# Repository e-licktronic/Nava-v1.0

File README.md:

# Nava-v1.0-code
An attempt to fix some of the remaining NAVA Firmware bugs and add some features I wanted for own use.

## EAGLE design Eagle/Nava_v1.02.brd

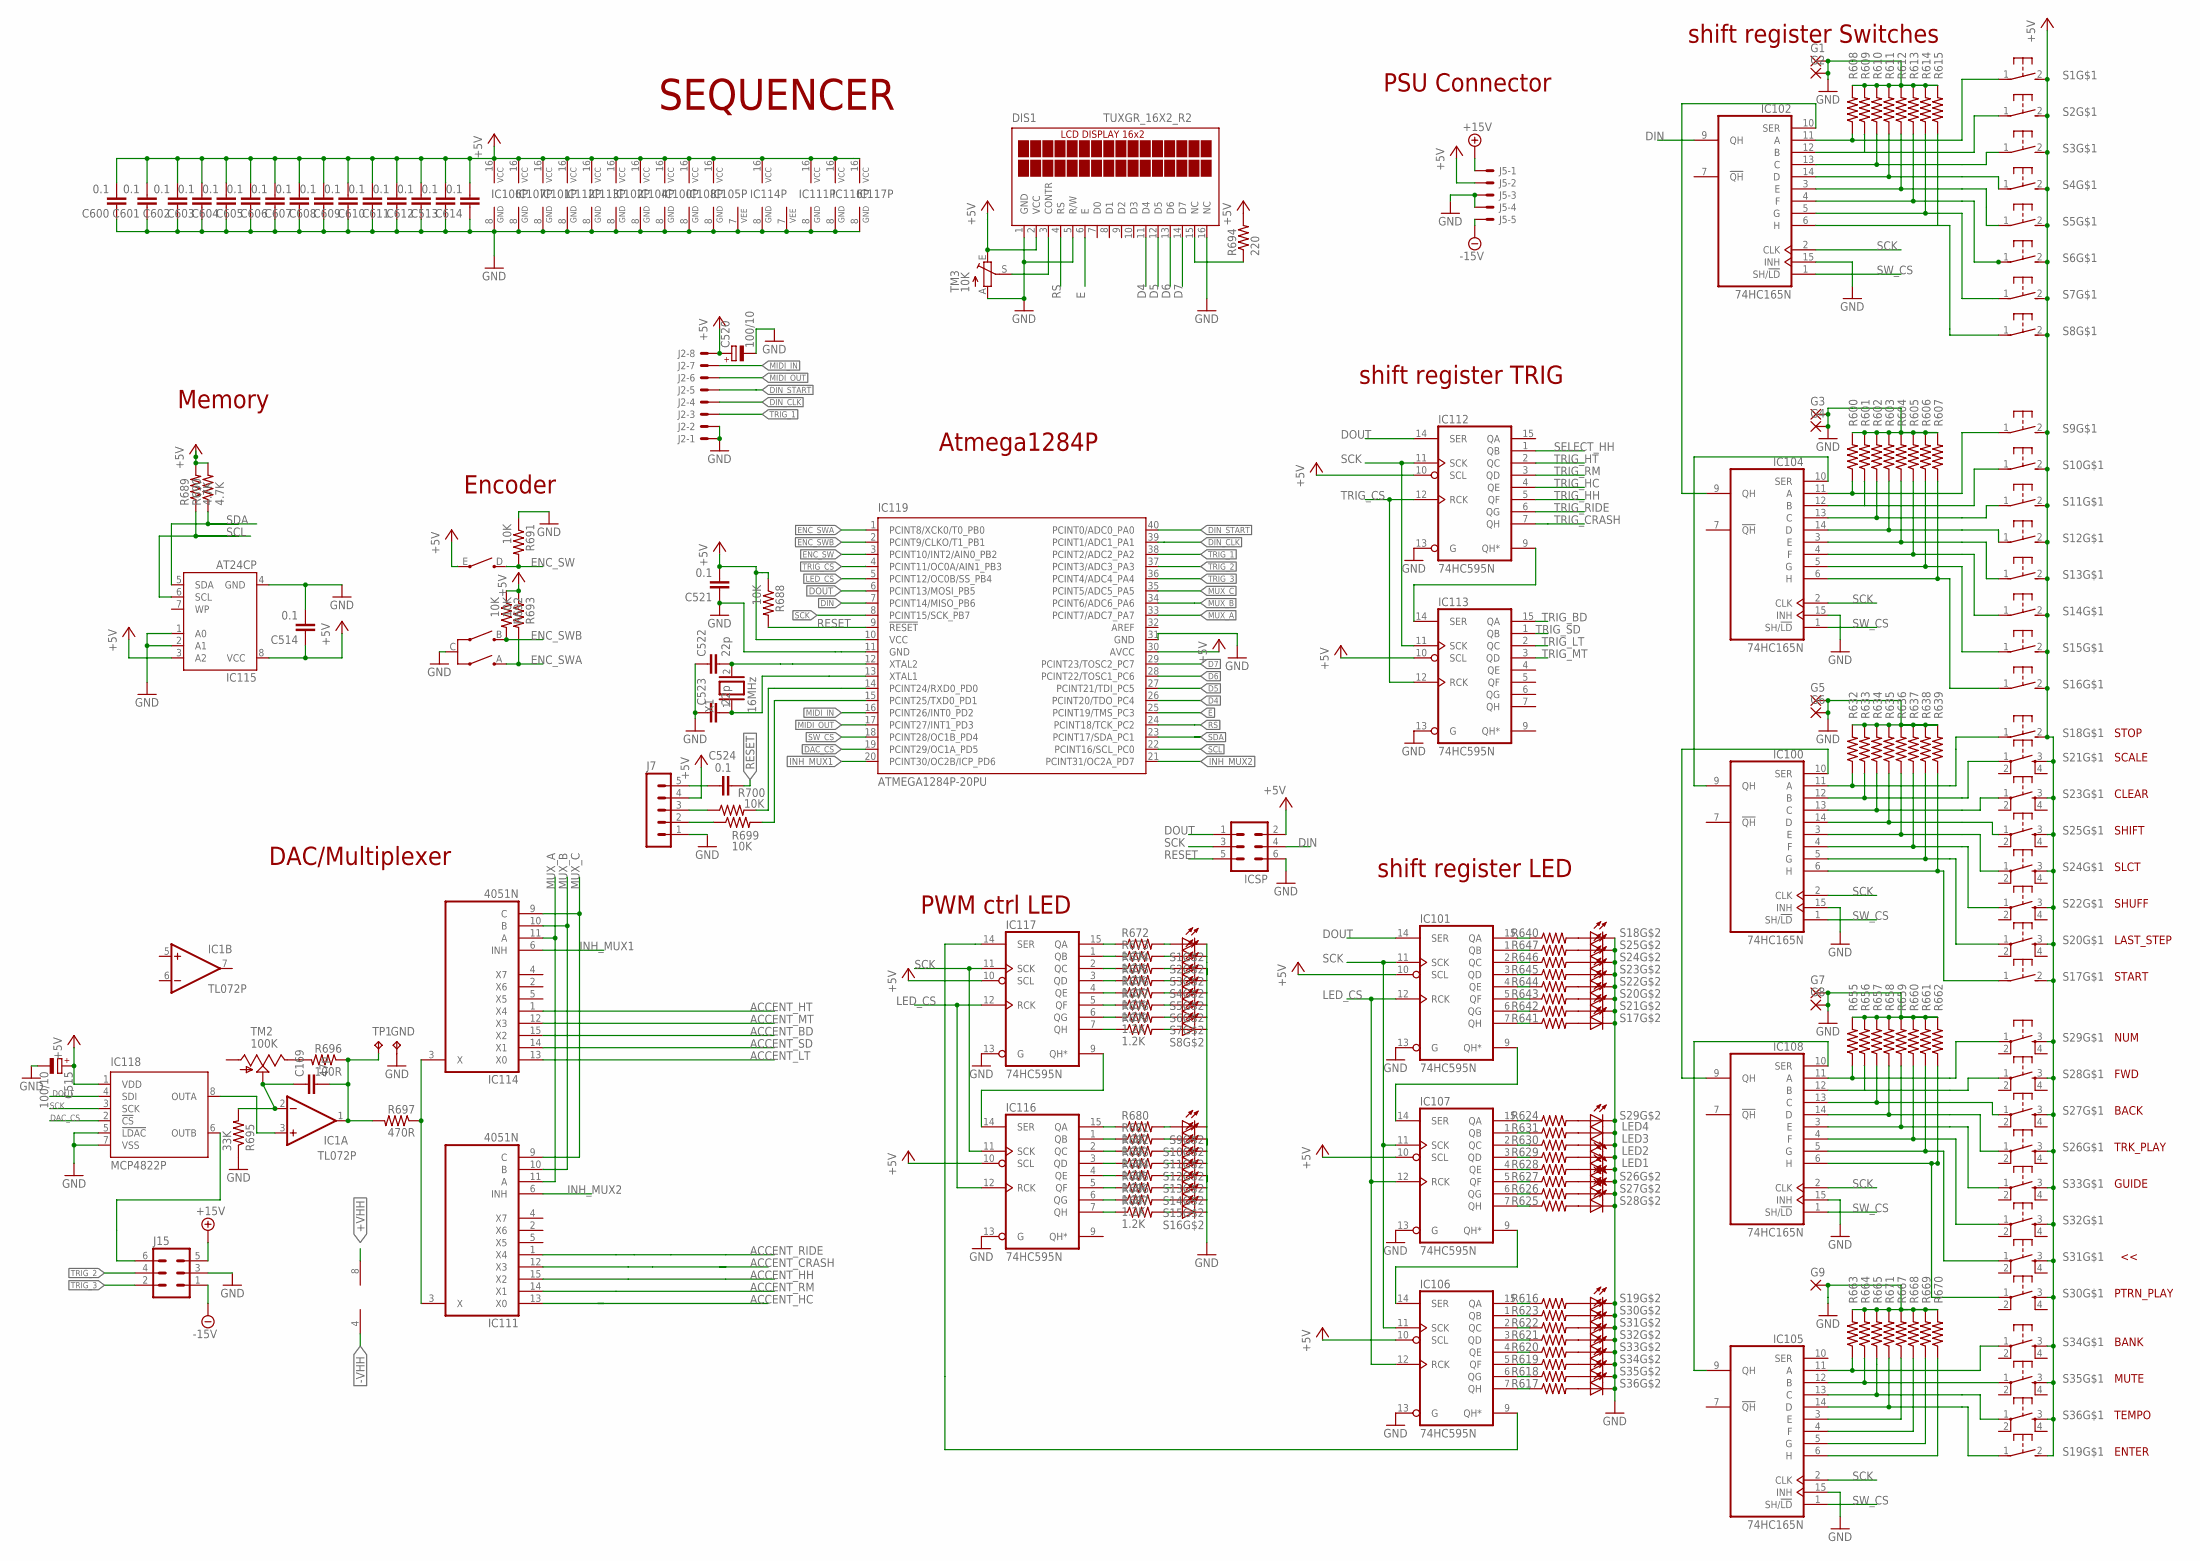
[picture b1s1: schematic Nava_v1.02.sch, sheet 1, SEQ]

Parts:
C169: 47p; C025-025X050
C513, C514, C521, C524, C600, C601, C602, C603, C604, C605, C606, C607, C608, C609, C610, C611, C612, C614: 0.1; C050-024X044
C515, C520: 100/10; E2-5
C522, C523: 22p; C025-025X050
DIS1: TUXGR_16X2_R2
G1, G2, G3, G4, G5, G6, G7, G8, G9: WIREPAD1,6/0,8; 1,6/0,8
GND: TPPAD1-13; P1-13
IC1: TL072P; DIL08
IC100, IC102, IC104, IC105, IC108: 74HC165N; DIL16
IC101, IC106, IC107, IC112, IC113, IC116, IC117: 74HC595N; DIL16
IC111, IC114: 4051N; DIL16
IC115: AT24CP; DIL08
IC118: MCP4822P; DIL8
IC119: ATMEGA1284P-20PU; DIL40
ICSP: MA03-2
J2: 22-27-2081-08; 6410-08
J5: KK-156-5
J7: MA05-1; MA05-1A
J15: MA03-2
LED1, LED2, LED3, LED4: LED3MM
R600, R601, R602, R603, R604, R605, R606, R607, R608, R609, R610, R611, R612, R613, R614, R615, R632, R633, R634, R635, R636, R637, R638, R639, R655, R656, R657, R658, R659, R660, R661, R662, R663, R664, R665, R667, R668, R669, R670, R671, R688, R691, R692, R693, R699, R700: 10K; 0207/7
R616, R617, R618, R619, R620, R621, R622, R623, R624, R625, R626, R627, R628, R629, R630, R631, R640, R641, R642, R643, R644, R645, R646, R647, R672, R673, R674, R675, R676, R677, R678, R679, R680, R681, R682, R683, R684, R685, R686, R687: 1.2K; 0207/7
R689, R690: 4.7K; 0207/7
R694: 220; 0207/7
R695: 33K; 0207/7
R696: 100R; 0207/7
R697: 470R; 0207/7
S1, S2, S3, S4, S5, S6, S7, S8, S9, S10, S11, S12, S13, S14, S15, S16, S17, S18, S19: MX1A_CHERRY_SW_LED"; MX1A-SW
S20, S21, S22, S23, S24, S25, S26, S27, S28, S29, S30, S31, S32, S33, S34, S35, S36: ZTSN_SW_LED"; SPH_SW
TM2: 100K; S64W
TM3: 10K; B25P
TP1: TPPAD1-13; P1-13
VR29: PEC16_ENCODER
X1: 16MHz; QS

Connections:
+5V: C513.2, C514.1, C515.+, C520.+, C521.2, C600.2, C601.2, C602.2, C603.2, C604.2, C605.2, C606.2, C607.2, C608.2, C609.2, C610.2, C611.2, C612.2, C614.2, DIS1.2 (VCC), IC100.16 (VCC), IC101.10 (SCL), IC101.16 (VCC), IC102.16 (VCC), IC104.16 (VCC), IC105.16 (VCC), IC106.10 (SCL), IC106.16 (VCC), IC107.10 (SCL), IC107.16 (VCC), IC108.16 (VCC), IC111.16 (VCC), IC112.10 (SCL), IC112.16 (VCC), IC113.10 (SCL), IC113.16 (VCC), IC114.16 (VCC), IC115.3 (A2), IC115.8 (VCC), IC116.10 (SCL), IC116.16 (VCC), IC117.10 (SCL), IC117.16 (VCC), IC118.1 (VDD), IC119.10 (VCC), IC119.30 (AVCC), ICSP.2, J2.8, J5.2, J7.4, R688.1, R689.2, R690.2, R692.1, R693.1, R694.2, S1.2 (S), S2.2 (S), S3.2 (S), S4.2 (S), S5.2 (S), S6.2 (S), S7.2 (S), S8.2 (S), S9.2 (S), S10.2 (S), S11.2 (S), S12.2 (S), S13.2 (S), S14.2 (S), S15.2 (S), S16.2 (S), S17.2 (S), S18.2 (S), S19.2 (S), S20.3 (S), S22.3 (S), S23.3 (S), S24.3 (S), S25.3 (S), S26.3 (S), S27.3 (S), S28.3 (S), S29.3 (S), S30.3 (S), S31.3 (S), S32.3 (S), S33.3 (S), S34.3 (S), S35.3 (S), S36.3 (S), TM3.E, VR29.E; also elsewhere on the board
+15V: J5.1, J15.5; also elsewhere on the board
+VHH: IC1.8 (V+); also elsewhere on the board
-15V: J5.5, J15.1; also elsewhere on the board
-VHH: IC1.4 (V-); also elsewhere on the board
ACCENT_BD: IC114.15 (X2); also elsewhere on the board
ACCENT_CRASH: IC111.12 (X3); also elsewhere on the board
ACCENT_HC: IC111.13 (X0); also elsewhere on the board
ACCENT_HH: IC111.15 (X2); also elsewhere on the board
ACCENT_HT: IC114.1 (X4); also elsewhere on the board
ACCENT_LT: IC114.13 (X0); also elsewhere on the board
ACCENT_MT: IC114.12 (X3); also elsewhere on the board
ACCENT_RIDE: IC111.1 (X4); also elsewhere on the board
ACCENT_RM: IC111.14 (X1); also elsewhere on the board
ACCENT_SD: IC114.14 (X1); also elsewhere on the board
D4: DIS1.11 (D4), IC119.26 (PCINT20/TDO_PC4)
D5: DIS1.12 (D5), IC119.27 (PCINT21/TDI_PC5)
D6: DIS1.13 (D6), IC119.28 (PCINT22/TOSC1_PC6)
D7: DIS1.14 (D7), IC119.29 (PCINT23/TOSC2_PC7)
DAC_CS: IC118.2 (!CS!), IC119.19 (PCINT29/OC1A_PD5)
DIN: IC102.9 (QH), IC119.7 (PCINT14/MISO_PB6), ICSP.4
DIN_CLK: IC119.39 (PCINT1/ADC1_PA1), J2.4
DIN_START: IC119.40 (PCINT0/ADC0_PA0), J2.5
DOUT: IC101.14 (SER), IC112.14 (SER), IC118.4 (SDI), IC119.6 (PCINT13/MOSI_PB5), ICSP.1
E: DIS1.6 (E), IC119.25 (PCINT19/TMS_PC3)
ENC_SW: IC119.3 (PCINT10/INT2/AIN0_PB2), R691.2, VR29.D
ENC_SWA: IC119.1 (PCINT8/XCK0/T0_PB0), R693.2, VR29.A
ENC_SWB: IC119.2 (PCINT9/CLKO/T1_PB1), R692.2, VR29.B
GND: C513.1, C514.2, C515.-, C520.-, C521.1, C522.1, C523.1, C600.1, C601.1, C602.1, C603.1, C604.1, C605.1, C606.1, C607.1, C608.1, C609.1, C610.1, C611.1, C612.1, C614.1, DIS1.1 (GND), DIS1.5 (R/W), DIS1.16 (NC), G1.1, G2.1, G3.1, G4.1, G5.1, G6.1, G7.1, G8.1, G9.1, GND.TP, IC100.8 (GND), IC100.15 (INH), IC101.8 (GND), IC101.13 (G), IC102.8 (GND), IC102.15 (INH), IC104.8 (GND), IC104.15 (INH), IC105.8 (GND), IC105.15 (INH), IC106.8 (GND), IC106.13 (G), IC107.8 (GND), IC107.13 (G), IC108.8 (GND), IC108.15 (INH), IC111.7 (VEE), IC111.8 (GND), IC112.8 (GND), IC112.13 (G), IC113.8 (GND), IC113.13 (G), IC114.7 (VEE), IC114.8 (GND), IC115.1 (A0), IC115.2 (A1), IC115.4 (GND), IC116.8 (GND), IC116.13 (G), IC117.8 (GND), IC117.13 (G), IC118.5 (!LDAC!), IC118.7 (VSS), IC119.11 (GND), IC119.31 (GND), ICSP.6, J2.1, J2.2, J5.3, J5.4, J7.1, J15.3, LED1.K (C), LED2.K (C), LED3.K (C), LED4.K (C), R600.2, R601.2, R602.2, R603.2, R604.2, R605.2, R606.2, R607.2, R608.2, R609.2, R610.2, R611.2, R612.2, R613.2, R614.2, R615.2, R632.2, R633.2, R634.2, R635.2, R636.2, R637.2, R638.2, R639.2, R655.2, R656.2, R657.2, R658.2, R659.2, R660.2, R661.2, R662.2, R663.2, R664.2, R665.2, R667.2, R668.2, R669.2, R670.2, R671.2, R691.1, R695.1, S1.K (C), S2.K (C), S3.K (C), S4.K (C), S5.K (C), S6.K (C), S7.K (C), S8.K (C), S9.K (C), S10.K (C), S11.K (C), S12.K (C), S13.K (C), S14.K (C), S15.K (C), S16.K (C), S17.K (C), S18.K (C), S19.K (C), S20.K (C), S21.K (C), S22.K (C), S23.K (C), S24.K (C), S25.K (C), S26.K (C), S27.K (C), S28.K (C), S29.K (C), S30.K (C), S31.K (C), S32.K (C), S33.K (C), S34.K (C), S35.K (C), S36.K (C), TM3.A, VR29.C; also elsewhere on the board
INH_MUX1: IC114.6 (INH), IC119.20 (PCINT30/OC2B/ICP_PD6)
INH_MUX2: IC111.6 (INH), IC119.21 (PCINT31/OC2A_PD7)
LED_CS: IC101.12 (RCK), IC106.12 (RCK), IC107.12 (RCK), IC116.12 (RCK), IC117.12 (RCK), IC119.5 (PCINT12/OC0B/SS_PB4)
MIDI_IN: IC119.16 (PCINT26/INT0_PD2), J2.7
MIDI_OUT: IC119.17 (PCINT27/INT1_PD3), J2.6
MUX_A: IC111.11 (A), IC114.11 (A), IC119.33 (PCINT7/ADC7_PA7)
MUX_B: IC111.10 (B), IC114.10 (B), IC119.34 (PCINT6/ADC6_PA6)
MUX_C: IC111.9 (C), IC114.9 (C), IC119.35 (PCINT5/ADC5_PA5)
unnamed: R624.2, S29.A
unnamed: R625.2, S28.A
unnamed: R626.2, S27.A
unnamed: R627.2, S26.A
unnamed: R647.2, S25.A
unnamed: R646.2, S24.A
unnamed: R645.2, S23.A
unnamed: R644.2, S22.A
unnamed: R642.2, S21.A
unnamed: R643.2, S20.A
unnamed: R640.2, S18.A
unnamed: R641.2, S17.A
unnamed: LED4.A, R631.2
unnamed: LED3.A, R630.2
unnamed: LED2.A, R629.2
unnamed: LED1.A, R628.2
unnamed: R616.2, S19.A
unnamed: R617.2, S36.A
unnamed: R618.2, S35.A
unnamed: R619.2, S34.A
unnamed: R620.2, S33.A
unnamed: R621.2, S32.A
unnamed: R622.2, S31.A
unnamed: R623.2, S30.A
unnamed: IC108.14 (D), R658.1, S26.1
unnamed: IC1.3 (+IN), IC118.8 (OUTA)
unnamed: IC117.15 (QA), R672.1
unnamed: IC117.1 (QB), R673.1
unnamed: IC117.2 (QC), R674.1
unnamed: IC117.3 (QD), R675.1
unnamed: IC117.4 (QE), R676.1
unnamed: IC117.5 (QF), R677.1
unnamed: IC117.6 (QG), R678.1
unnamed: IC117.7 (QH), R679.1
unnamed: IC116.14 (SER), IC117.9 (QH*)
unnamed: IC116.15 (QA), R680.1
unnamed: IC116.1 (QB), R681.1
unnamed: IC116.2 (QC), R682.1
unnamed: IC116.3 (QD), R683.1
unnamed: IC116.4 (QE), R684.1
unnamed: IC116.5 (QF), R685.1
unnamed: IC116.6 (QG), R686.1
unnamed: IC116.7 (QH), R687.1
unnamed: R680.2, S9.A
unnamed: R681.2, S10.A
unnamed: R682.2, S11.A
unnamed: R683.2, S12.A
unnamed: R684.2, S13.A
unnamed: R685.2, S14.A
unnamed: R686.2, S15.A
unnamed: R687.2, S16.A
unnamed: R672.2, S1.A
unnamed: R673.2, S2.A
unnamed: R674.2, S3.A
unnamed: R675.2, S4.A
unnamed: R676.2, S5.A
unnamed: R677.2, S6.A
unnamed: R678.2, S7.A
unnamed: R679.2, S8.A
unnamed: IC106.9 (QH*), IC117.14 (SER)
unnamed: IC118.6 (OUTB), J15.6
unnamed: IC119.15 (PCINT25/TXD0_PD1), R699.2
unnamed: IC119.14 (PCINT24/RXD0_PD0), R700.2
unnamed: C522.2, IC119.12 (XTAL2), X1.2
unnamed: C523.2, IC119.13 (XTAL1), X1.1
unnamed: IC102.11 (A), R608.1, S1.1
unnamed: IC102.12 (B), R609.1, S2.1
unnamed: IC102.13 (C), R610.1, S3.1
unnamed: IC102.14 (D), R611.1, S4.1
unnamed: IC102.3 (E), R612.1, S5.1
unnamed: IC102.4 (F), R613.1, S6.1
unnamed: IC102.5 (G), R614.1, S7.1
unnamed: IC102.6 (H), R615.1, S8.1
unnamed: IC104.11 (A), R600.1, S9.1
unnamed: IC104.12 (B), R601.1, S10.1
unnamed: IC104.13 (C), R602.1, S11.1
unnamed: IC104.14 (D), R603.1, S12.1
unnamed: IC104.3 (E), R604.1, S13.1
unnamed: IC104.4 (F), R605.1, S14.1
unnamed: IC104.5 (G), R606.1, S15.1
unnamed: IC104.6 (H), R607.1, S16.1
unnamed: IC100.11 (A), R632.1, S18.1
unnamed: IC100.12 (B), R633.1, S21.1
unnamed: IC100.13 (C), R634.1, S23.1
unnamed: IC100.14 (D), R635.1, S25.1
unnamed: IC100.3 (E), R636.1, S24.1
unnamed: IC100.4 (F), R637.1, S22.1
unnamed: IC100.5 (G), R638.1, S20.1
unnamed: IC102.10 (SER), IC104.9 (QH)
unnamed: IC100.9 (QH), IC104.10 (SER)
unnamed: IC100.6 (H), R639.1, S17.1
unnamed: IC111.3 (X), IC114.3 (X), R697.1
unnamed: IC101.15 (QA), R640.1
unnamed: IC100.10 (SER), IC108.9 (QH)
unnamed: IC108.11 (A), R655.1, S29.1
unnamed: IC108.12 (B), R656.1, S28.1
unnamed: IC108.13 (C), R657.1, S27.1
unnamed: IC108.3 (E), R659.1, S33.1
unnamed: IC108.4 (F), R660.1, S32.1
unnamed: IC108.5 (G), R661.1, S31.1
unnamed: IC108.6 (H), R662.1, S30.1
unnamed: IC101.1 (QB), R647.1
unnamed: IC105.9 (QH), IC108.10 (SER)
unnamed: IC101.2 (QC), R646.1
unnamed: IC105.11 (A), R663.1, S34.1
unnamed: IC105.12 (B), R664.1, S35.1
unnamed: IC105.13 (C), R665.1, S36.1
unnamed: IC105.14 (D), R671.1, S19.1
unnamed: IC105.3 (E), R667.1
unnamed: IC105.4 (F), R668.1
unnamed: IC105.5 (G), R669.1
unnamed: IC105.6 (H), R670.1
unnamed: IC101.3 (QD), R645.1
unnamed: IC101.4 (QE), R644.1
unnamed: IC101.5 (QF), R643.1
unnamed: IC101.6 (QG), R642.1
unnamed: IC101.7 (QH), R641.1
unnamed: IC107.15 (QA), R624.1
unnamed: IC107.1 (QB), R631.1
unnamed: IC107.2 (QC), R630.1
unnamed: IC107.3 (QD), R629.1
unnamed: IC107.4 (QE), R628.1
unnamed: IC107.5 (QF), R627.1
unnamed: IC107.6 (QG), R626.1
unnamed: IC107.7 (QH), R625.1
unnamed: IC101.9 (QH*), IC107.14 (SER)
unnamed: IC106.14 (SER), IC107.9 (QH*)
unnamed: IC106.15 (QA), R616.1
unnamed: IC106.1 (QB), R623.1
unnamed: IC106.2 (QC), R622.1
unnamed: IC106.3 (QD), R621.1
unnamed: IC106.4 (QE), R620.1
unnamed: IC106.5 (QF), R619.1
unnamed: IC106.6 (QG), R618.1
unnamed: IC106.7 (QH), R617.1
unnamed: R696.2, TM2.E
unnamed: C169.2, IC1.1 (OUT), R696.1, R697.2, TP1.TP
unnamed: C169.1, IC1.2 (-IN), R695.2, TM2.S
unnamed: DIS1.15 (NC), R694.1
unnamed: DIS1.3 (CONTR), TM3.S
unnamed: IC112.9 (QH*), IC113.14 (SER)
unnamed: C524.2, J7.5
unnamed: J7.3, R700.1
unnamed: J7.2, R699.1
RESET: C524.1, IC119.9 (!RESET), ICSP.5, R688.2
RS: DIS1.4 (RS), IC119.24 (PCINT18/TCK_PC2)
SCK: IC100.2 (CLK), IC101.11 (SCK), IC102.2 (CLK), IC104.2 (CLK), IC105.2 (CLK), IC106.11 (SCK), IC107.11 (SCK), IC108.2 (CLK), IC112.11 (SCK), IC113.11 (SCK), IC116.11 (SCK), IC117.11 (SCK), IC118.3 (SCK), IC119.8 (PCINT15/SCK_PB7), ICSP.3
SCL: IC115.6 (SCL), IC119.22 (PCINT16/SCL_PC0), R689.1
SDA: IC115.5 (SDA), IC119.23 (PCINT17/SDA_PC1), R690.1
SELECT_HH: IC112.1 (QB); also elsewhere on the board
SW_CS: IC100.1 (SH/!LD), IC102.1 (SH/!LD), IC104.1 (SH/!LD), IC105.1 (SH/!LD), IC108.1 (SH/!LD), IC119.18 (PCINT28/OC1B_PD4)
TRIG_1: IC119.38 (PCINT2/ADC2_PA2), J2.3
TRIG_2: IC119.37 (PCINT3/ADC3_PA3), J15.4
TRIG_3: IC119.36 (PCINT4/ADC4_PA4), J15.2
TRIG_BD: IC113.15 (QA); also elsewhere on the board
TRIG_CRASH: IC112.7 (QH); also elsewhere on the board
TRIG_CS: IC112.12 (RCK), IC113.12 (RCK), IC119.4 (PCINT11/OC0A/AIN1_PB3)
TRIG_HC: IC112.4 (QE); also elsewhere on the board
TRIG_HH: IC112.5 (QF); also elsewhere on the board
TRIG_HT: IC112.2 (QC); also elsewhere on the board
TRIG_LT: IC113.2 (QC); also elsewhere on the board
TRIG_MT: IC113.3 (QD); also elsewhere on the board
TRIG_RIDE: IC112.6 (QG); also elsewhere on the board
TRIG_RM: IC112.3 (QD); also elsewhere on the board
TRIG_SD: IC113.1 (QB); also elsewhere on the board

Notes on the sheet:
Memory
Encoder
Atmega1284P
DAC/Multiplexer
PWM ctrl LED
shift register LED
shift register TRIG
shift register Switches
SEQUENCER
PSU Connector
STOP
SCALE
CLEAR
SHIFT
SLCT
SHUFF
LAST_STEP
START
NUM
FWD
BACK
TRK_PLAY
GUIDE
PTRN_PLAY
BANK
MUTE
TEMPO
ENTER

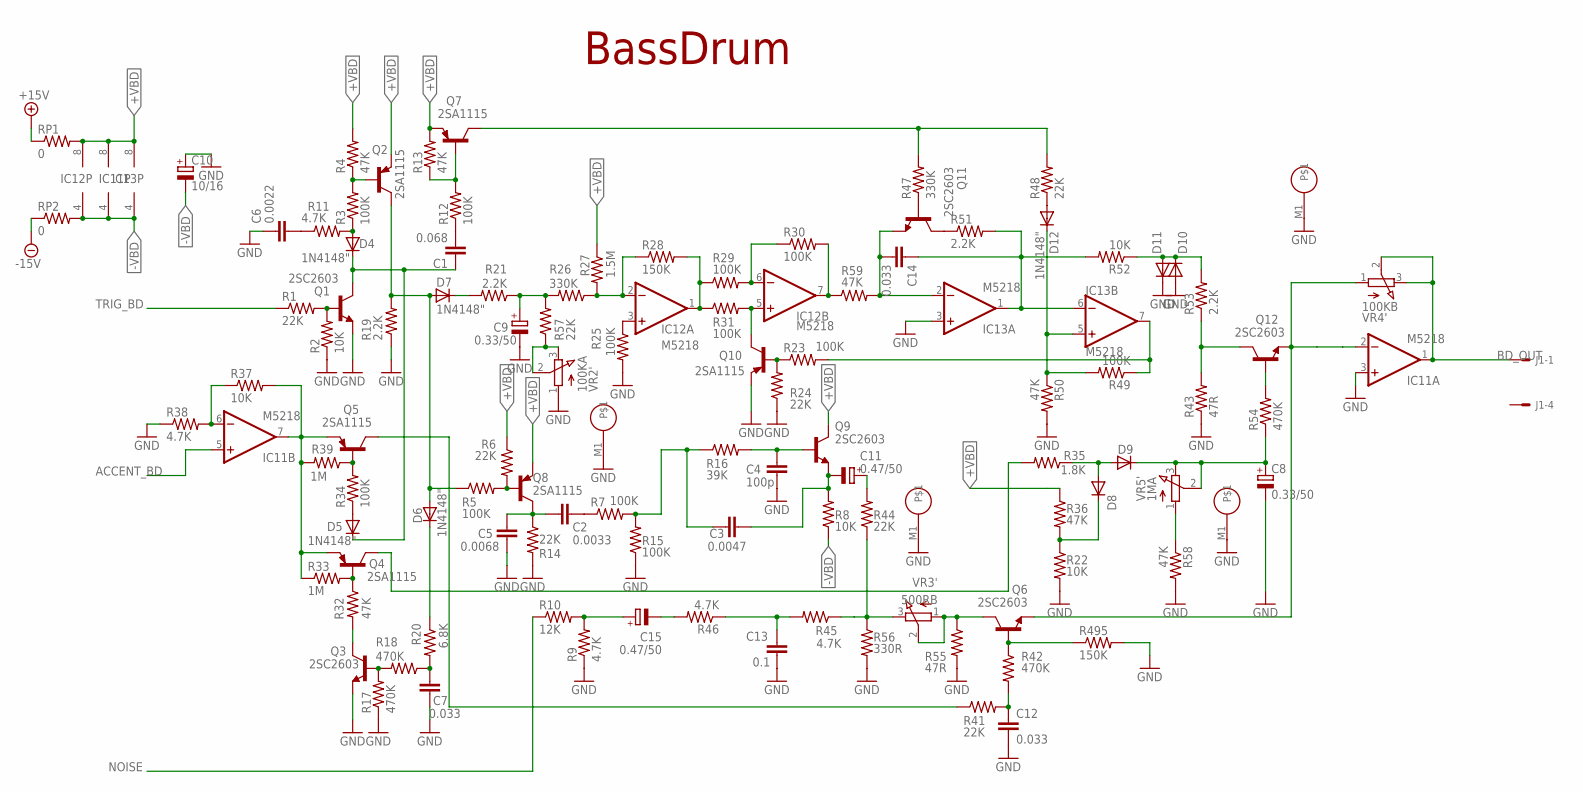
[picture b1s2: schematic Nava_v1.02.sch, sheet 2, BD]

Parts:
C1: 0.068; C050-025X075
C2: 0.0033; C050-025X075
C3: 0.0047; C050-025X075
C4: 100p; C050-025X075
C5: 0.0068; C050-025X075
C6: 0.0022; C050-025X075
C7, C12, C14: 0.033; C050-025X075
C8, C9: 0.33/50; E2-5
C10: 10/16; E2-5
C11, C15: 0.47/50; E2-5
C13: 0.1; C050-025X075
D4, D5, D6, D7, D8, D9, D10, D11, D12: 1N4148"; DO35-7C
IC11, IC12, IC13: M5218; SIL8
J1: 22-27-2041-04; 6410-04
Q1, Q3, Q6, Q9, Q11, Q12: 2SC2603; TO92-ECB
Q2, Q4, Q5, Q7, Q8, Q10: 2SA1115; TO92-ECB-PNP
R1, R6, R14, R24, R41, R44, R48, R57: 22K; 0207/7
R2, R8, R22, R37, R52: 10K; 0207/7
R3, R5, R7, R12, R15, R23, R25, R29, R30, R31, R34, R49: 100K; 0207/7
R4, R13, R32, R36, R50, R58, R59: 47K; 0207/7
R9, R11, R38, R45, R46: 4.7K; 0207/7
R10: 12K; 0207/7
R16: 39K; 0207/7
R17, R18, R42, R54: 470K; 0207/7
R19, R21, R51, R53: 2.2K; 0207/7
R20: 6.8K; 0207/7
R26, R47: 330K; 0207/7
R27: 1.5M; 0207/7
R28, R495: 150K; 0207/7
R33, R39: 1M; 0207/7
R35: 1.8K; 0207/7
R43, R55: 47R; 0207/7
R56: 330R; 0207/7
RP1, RP2: 0; 0207/7
VR2: 100KA; EVUF
VR3: 500RB; EVUF
VR4: 100KB; EVUF
VR5: 1MA; EVUF

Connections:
+15V: RP1.1; also elsewhere on the board
+VBD: IC11.8 (V+), IC12.8 (V+), IC13.8 (V+), Q2.E, Q7.E, Q8.E, Q9.C, R4.2, R6.1, R13.2, R27.1, R36.1, RP1.2
-15V: RP2.1; also elsewhere on the board
-VBD: C10.-, IC11.4 (V-), IC12.4 (V-), IC13.4 (V-), R8.1, RP2.2
ACCENT_BD: IC11.5 (+IN); also elsewhere on the board
BD_OUT: IC11.1 (OUT), J1.1, VR4.2 (S), VR4.3 (E)
GND: C4.2, C5.1, C6.1, C7.1, C8.-, C9.-, C10.+, C12.2, C13.2, D10.A, D11.C, IC11.3 (+IN), IC13.3 (+IN), Q1.E, Q3.E, Q10.E, R2.1, R9.1, R14.2, R15.1, R17.1, R19.1, R22.2, R24.1, R25.2, R38.1, R43.1, R50.2, R55.2, R56.2, R58.2, R495.2, VR2.1 (A), VR2.M1, VR3.M1, VR4.M1, VR5.M1; also elsewhere on the board
unnamed: Q1.B, R1.2, R2.2
unnamed: Q2.B, R3.2, R4.1
unnamed: Q5.B, R34.2, R39.1
unnamed: Q4.B, R32.1, R33.2
unnamed: Q3.B, R17.2, R18.2
unnamed: C7.2, R18.1, R20.2
unnamed: C2.2, C5.2, Q8.C, R14.1
unnamed: Q8.B, R5.2, R6.2
unnamed: D4.A, R3.1, R11.2
unnamed: D5.A, R34.1
unnamed: D6.A, D7.A, Q2.C, R5.1, R19.2
unnamed: C1.1, D4.C, D5.C, Q1.C
unnamed: Q7.B, R12.2, R13.1
unnamed: Q3.C, R32.2
unnamed: C6.2, R11.1
unnamed: C1.2, R12.1
unnamed: D6.C, R20.1
unnamed: D7.C, R21.2
unnamed: C9.+, R21.1, R26.2, R57.2
unnamed: R57.1, VR2.2 (S), VR2.3 (E)
unnamed: IC12.2 (-IN), R26.1, R27.2, R28.1
unnamed: IC11.7 (OUT), Q4.E, Q5.E, R33.1, R37.2, R39.2
unnamed: IC11.6 (-IN), R37.1, R38.2
unnamed: IC12.3 (+IN), R25.1
unnamed: IC12.1 (OUT), R28.2, R29.1, R31.1
unnamed: IC12.5 (+IN), Q10.C, R31.2
unnamed: IC12.6 (-IN), R29.2, R30.1
unnamed: IC12.7 (OUT), R30.2, R59.1
unnamed: Q10.B, R23.1, R24.2
unnamed: Q11.B, R47.1
unnamed: Q7.C, R47.2, R48.2
unnamed: C14.2, IC13.2 (-IN), Q11.E, R59.2
unnamed: Q11.C, R51.1
unnamed: D12.A, R48.1
unnamed: C14.1, IC13.1 (OUT), IC13.6 (-IN), R51.2, R52.2
unnamed: IC13.7 (OUT), R23.2, R49.1
unnamed: D12.C, IC13.5 (+IN), R49.2, R50.1
unnamed: D10.C, D11.A, R52.1, R53.2
unnamed: Q12.B, R54.2
unnamed: Q12.C, R43.2, R53.1
unnamed: C8.+, D9.C, R54.1, VR5.2 (S), VR5.3 (E)
unnamed: D8.C, R22.1, R36.2
unnamed: D8.A, D9.A, R35.1
unnamed: R58.1, VR5.1 (A)
unnamed: Q4.C, R35.2
unnamed: C2.1, R7.1
unnamed: C3.1, R7.2, R15.2, R16.1
unnamed: C4.1, Q9.B, R16.2
unnamed: C3.2, C11.-, Q9.E, R8.2
unnamed: C11.+, R44.2
unnamed: C15.+, R9.2, R10.2
unnamed: Q6.B, R42.1, R495.1
unnamed: C12.1, R41.2, R42.2
unnamed: C15.-, R46.2
unnamed: C13.1, R45.2, R46.1
unnamed: R44.1, R45.1, R56.1, VR3.3 (E)
unnamed: Q6.C, R55.1, VR3.1 (A), VR3.2 (S)
unnamed: Q5.C, R41.1
unnamed: IC11.2 (-IN), Q6.E, Q12.E, VR4.1 (A)
NOISE: R10.1; also elsewhere on the board
TRIG_BD: R1.1; also elsewhere on the board

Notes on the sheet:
BassDrum

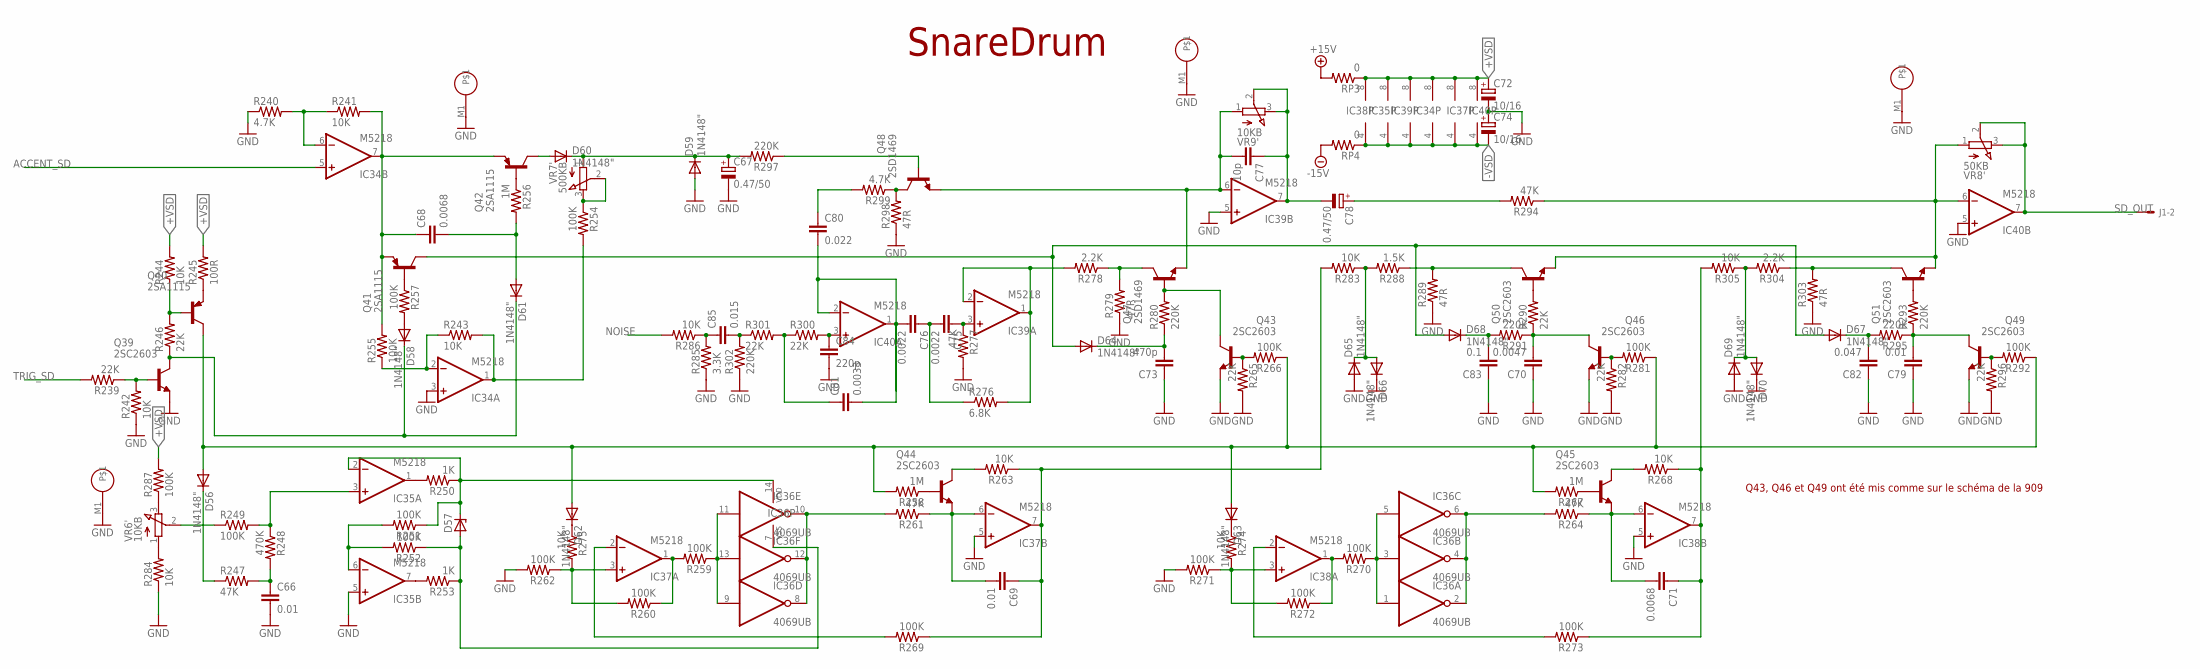
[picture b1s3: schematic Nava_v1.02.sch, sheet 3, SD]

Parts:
C66, C69, C79: 0.01; C050-025X075
C67, C78: 0.47/50; E2-5
C68, C71: 0.0068; C050-025X075
C70: 0.0047; C050-025X075
C72, C74: 10/16; E2-5
C73: 470p; C050-025X075
C75, C76: 0.0022; C050-025X075
C77: 10p; C050-025X075
C80: 0.022; C050-025X075
C81: 0.0033; C050-025X075
C82: 0.047; C050-025X075
C83: 0.1; C050-025X075
C84: 220p; C050-025X075
C85: 0.015; C050-025X075
D56, D58, D59, D60, D61, D62, D63, D64, D65, D66, D67, D68, D69, D70: 1N4148"; DO35-7C
D57: ZENER-DIODE; DO41-7
IC34, IC35, IC37, IC38, IC39, IC40: M5218; SIL8
IC36: 4069UB; DIL14
J1: 22-27-2041-04; 6410-04
Q39, Q43, Q44, Q45, Q46, Q49, Q50, Q51: 2SC2603; TO92-ECB
Q40, Q41, Q42: 2SA1115; TO92-ECB-PNP
Q47, Q48: 2SD1469; TO-3
R239, R246, R265, R282, R290, R296, R300, R301: 22K; 0207/7
R240, R299: 4.7K; 0207/7
R241, R242, R243, R244, R263, R268, R274, R275, R283, R284, R286, R305: 10K; 0207/7
R245: 100R; 0207/7
R247, R261, R264, R277, R294: 47K; 0207/7
R248: 470K; 0207/7
R249, R251, R252, R254, R255, R257, R259, R260, R262, R266, R269, R270, R271, R272, R273, R281, R287, R292: 100K; 0207/7
R250, R253: 1K; 0207/7
R256, R258, R267: 1M; 0207/7
R276: 6.8K; 0207/7
R278, R304: 2.2K; 0207/7
R279, R289, R298, R303: 47R; 0207/7
R280, R291, R293, R295, R297, R302: 220K; 0207/7
R285: 3.3K; 0207/7
R288: 1.5K; 0207/7
RP3, RP4: 0; 0207/7
VR6, VR9: 10KB; EVUF
VR7: 500KB; EVUF
VR8: 50KB; EVUF

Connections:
+15V: RP3.2; also elsewhere on the board
+VSD: C72.+, IC34.8 (V+), IC35.8 (V+), IC37.8 (V+), IC38.8 (V+), IC39.8 (V+), IC40.8 (V+), R244.2, R245.2, R287.2, RP3.1
-15V: RP4.2; also elsewhere on the board
-VSD: C74.-, IC34.4 (V-), IC35.4 (V-), IC37.4 (V-), IC38.4 (V-), IC39.4 (V-), IC40.4 (V-), RP4.1
ACCENT_SD: IC34.5 (+IN); also elsewhere on the board
GND: C66.2, C67.-, C70.1, C72.-, C73.1, C74.+, C79.1, C82.1, C83.1, C84.2, D59.A, D65.A, D66.C, D69.A, D70.C, IC34.3 (+IN), IC35.5 (+IN), IC37.5 (+IN), IC38.5 (+IN), IC39.5 (+IN), IC40.5 (+IN), Q39.E, Q43.E, Q46.E, Q49.E, R240.1, R242.1, R262.2, R265.2, R271.2, R277.2, R279.1, R282.2, R284.1, R285.1, R289.1, R296.2, R298.1, R302.1, R303.1, VR6.M1, VR7.M1, VR8.M1, VR9.M1; also elsewhere on the board
unnamed: Q50.B, R290.2
unnamed: Q46.B, R281.2, R282.1
unnamed: C70.2, Q46.C, R290.1, R291.1
unnamed: Q43.C, Q47.B, R280.2
unnamed: Q43.B, R265.1, R266.2
unnamed: C73.2, D64.C, R280.1
unnamed: C83.2, D68.C, R291.2
unnamed: D65.C, D66.A, R283.1, R288.2
unnamed: Q50.C, R288.1, R289.2
unnamed: Q51.B, R293.2
unnamed: Q49.B, R292.2, R296.1
unnamed: C79.2, Q49.C, R293.1, R295.1
unnamed: C82.2, D67.C, R295.2
unnamed: D69.C, D70.A, R304.2, R305.1
unnamed: Q51.C, R303.2, R304.1
unnamed: IC40.6 (-IN), Q50.E, Q51.E, R294.1, VR8.1 (A)
unnamed: Q45.B, R267.1
unnamed: C71.1, IC38.7 (OUT), R268.1, R273.1, R305.2
unnamed: C71.2, IC38.6 (-IN), Q45.E, R264.1
unnamed: Q45.C, R268.2
unnamed: IC36.2 (O), IC36.4 (O), IC36.6 (O), R264.2
unnamed: IC36.1 (I), IC36.3 (I), IC36.5 (I), R270.1
unnamed: IC38.1 (OUT), R270.2, R272.1
unnamed: IC38.3 (+IN), R271.1, R272.2, R274.2
unnamed: IC38.2 (-IN), R273.2
unnamed: D63.C, R274.1
unnamed: Q44.B, R258.1
unnamed: C69.2, IC37.6 (-IN), Q44.E, R261.1
unnamed: Q44.C, R263.2
unnamed: IC36.8 (O), IC36.10 (O), IC36.12 (O), R261.2
unnamed: IC36.9 (I), IC36.11 (I), IC36.13 (I), R259.1
unnamed: IC37.1 (OUT), R259.2, R260.1
unnamed: IC37.3 (+IN), R260.2, R262.1, R275.2
unnamed: IC37.2 (-IN), R269.2
unnamed: D62.C, R275.1
unnamed: D56.A, D62.A, D63.A, Q40.C, R258.2, R266.1, R267.2, R281.1, R292.1
unnamed: IC35.1 (OUT), R250.2
unnamed: IC35.7 (OUT), R253.2
unnamed: IC35.6 (-IN), R251.2, R252.2
unnamed: D57.A, IC36.7 (VSS), R252.1, R253.1
unnamed: D57.C, IC35.2 (-IN), IC36.14 (VDD), R250.1, R251.1
unnamed: R287.1, VR6.3 (E)
unnamed: R284.2, VR6.1 (A)
unnamed: R249.1, VR6.2 (S)
unnamed: IC35.3 (+IN), R248.1, R249.2
unnamed: C66.1, R247.2, R248.2
unnamed: D56.C, R247.1
unnamed: Q47.C, R278.1, R279.2
unnamed: C77.2, IC39.6 (-IN), Q47.E, Q48.E, VR9.1 (A)
unnamed: C77.1, C78.-, IC39.7 (OUT), VR9.2 (S), VR9.3 (E)
unnamed: C78.+, R294.2
unnamed: IC39.1 (OUT), IC39.2 (-IN), R276.2, R278.2
unnamed: D64.A, D67.A, D68.A, Q41.C
unnamed: C75.1, IC39.3 (+IN), R277.1
unnamed: C75.2, C76.1, R276.1
unnamed: C76.2, C80.2, C81.2, IC40.1 (OUT), IC40.2 (-IN)
unnamed: C84.1, IC40.3 (+IN), R300.2
unnamed: C81.1, R300.1, R301.2
unnamed: C85.2, R301.1, R302.2
unnamed: C85.1, R285.2, R286.1
unnamed: Q48.C, R298.2, R299.1
unnamed: C80.1, R299.2
unnamed: C67.+, D59.C, D60.C, R297.2, VR7.1 (A)
unnamed: R254.1, VR7.2 (S), VR7.3 (E)
unnamed: D60.A, Q42.C
unnamed: Q42.B, R256.1
unnamed: Q41.B, R257.1
unnamed: Q48.B, R297.1
unnamed: D58.A, R257.2
unnamed: IC34.6 (-IN), R240.2, R241.1
unnamed: C68.1, IC34.7 (OUT), Q41.E, Q42.E, R241.2, R255.2
unnamed: IC34.2 (-IN), R243.1, R255.1
unnamed: IC34.1 (OUT), R243.2, R254.2
unnamed: C68.2, D61.A, R256.2
unnamed: D58.C, D61.C, Q39.C, R246.1
unnamed: Q40.E, R245.1
unnamed: Q40.B, R244.1, R246.2
unnamed: Q39.B, R239.1, R242.2
NOISE: R286.2; also elsewhere on the board
R263: C69.1, IC37.7 (OUT), R263.1, R269.1, R283.2
SD_OUT: IC40.7 (OUT), J1.2, VR8.2 (S), VR8.3 (E)
TRIG_SD: R239.2; also elsewhere on the board

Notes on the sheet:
SnareDrum
Q43, Q46 et Q49 ont été mis comme sur le schéma de la 909
